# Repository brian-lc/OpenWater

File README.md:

# OpenWater
This is an open source hardware project. It is published under the CERN OpenHardware License. https://www.ohwr.org/documents/294

#Note!
This is very much a work in progress. All designs are subject to change.

## Goal
To create and share an open source water monitoring system that was capable of measuring water temperature, pH, and ORP. 

This repo contains all the hardware, software, 3D models, and instructions on how to create your own version. 

## Bill of Materials (all versions)
https://docs.google.com/spreadsheets/d/1hH_PX7qE9Eqqa5zU-xhwlhM-gbqpwk3e61Kn0q8U03g/edit?usp=sharing

# History

## V3 - Pelican case - WIP
This version rethinks the whole approach and tries to again use a simple enclosure to house the electronics and keep things water-tight. Forget submerged housings and dealing with buoyancy. This will use some foam and the Pelican case to keep the device on top of the water. It'll be bigger but it will also allow the placement of a solar panel on top. 

## V2 - Inflatable 
This design throws away the idea that the enclosure needs to be rigid. Using a flexible tubing (originally designed for industrial processing) I created an enclosure that could be inflated/deflated to adjust for buoyancy. What I learned was that 1) buoyancy is hard to get right when it's a DIY project. Even the slightest off center mass (like a cable on one side) could cause the whole setup to list. Also, USB cables rust. Also also, making something water tight is hard. The first time I floated this in an over-night test the whole inside filled with water because the air pressure stem didn't have enough back-pressure to keep the water out. Luckily none of the electronics were harmed. 

## V1 - Blender Bottle
My first attempt at a cheap ($11 USD) enclosure using an off-the-shelf blender bottle. With just a few components this design came together well but it proved to be too difficult to service the battery. Also, the cabling situation was a nightmare. The probes each come with about 5 feet of coax. Dealing with it is a real pain. 

### Resources and other projects
https://www.voltaicsystems.com/blog/building-solar-powered-cloud-connected-devices/

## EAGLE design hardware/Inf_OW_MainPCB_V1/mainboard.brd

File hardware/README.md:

## Hardware
Here are the eagle source files for the OpenWater PCB. It's a very straightforward design. There are no parts on the PCB itself except for a few pull up resistors (which are not technically needed if you rely on the ones from the internal temp/humidity board by Sparkfun). Also, it has two mount holes placed for easy fastening to an enclosure. See 3D files for details.

The gerbers included here are for version 2 since I used Eagle for V2. For the first version I used Upverter. You can find that project here: https://upverter.com/breakpointer/075962a4a041eaf9/OpenWater_v1/

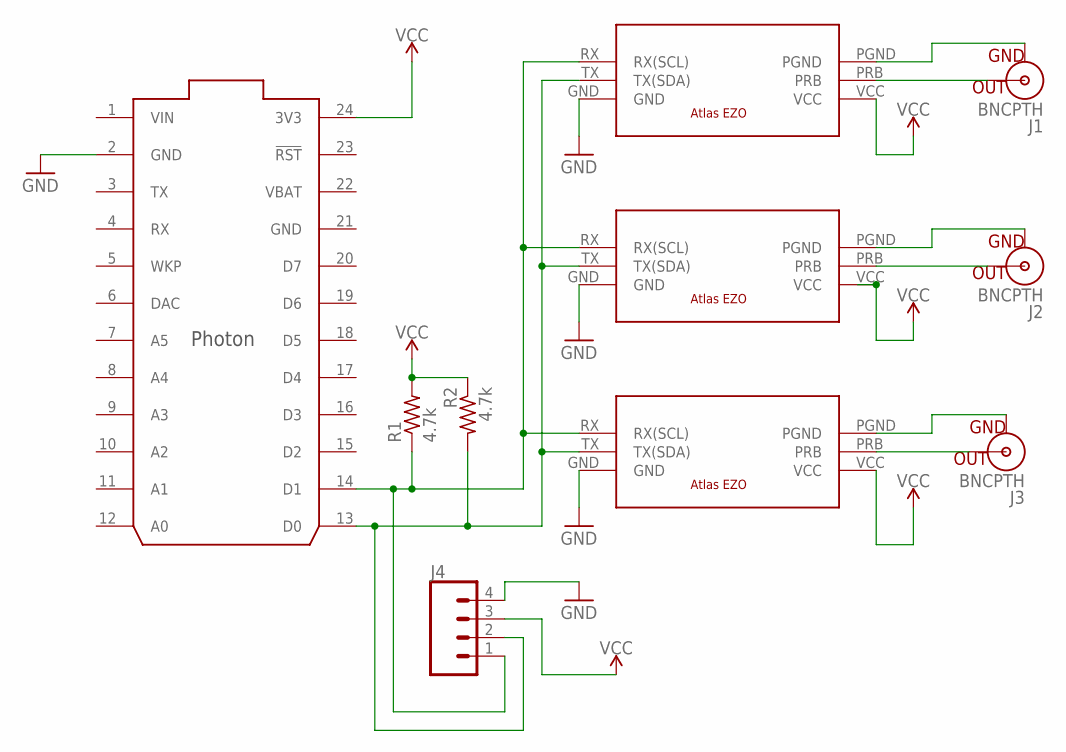
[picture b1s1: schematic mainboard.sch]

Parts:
J1, J2, J3: BNCPTH; BNC
J4: CONN_04; 1X04
R1, R2: 4.7k; 0207/7
U$1: PHOTON_SMD
U$2, U$3, U$4: ATLSCI_EZO; ATLAS_SCI_EZO

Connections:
GND: J4.4, U$1.2 (GND), U$1.21 (GND), U$2.GND, U$3.GND, U$4.GND
unnamed: J4.1, R1.1, U$1.14 (D1), U$2.RX (RX(SCL)), U$3.RX (RX(SCL)), U$4.RX (RX(SCL))
unnamed: J4.2, R2.2, U$1.13 (D0), U$2.TX (TX(SDA)), U$3.TX (TX(SDA)), U$4.TX (TX(SDA))
unnamed: J2.S (OUT), U$3.PRB
unnamed: J2.GND, U$3.PGND
unnamed: J1.S (OUT), U$2.PRB
unnamed: J1.GND, U$2.PGND
unnamed: J3.S (OUT), U$4.PRB
unnamed: J3.GND, U$4.PGND
VBAT: U$1.22 (VBAT)
VCC: J4.3, R1.2, R2.1, U$1.24 (3V3), U$2.VCC, U$3.VCC, U$4.VCC
VIN: U$1.1 (VIN)

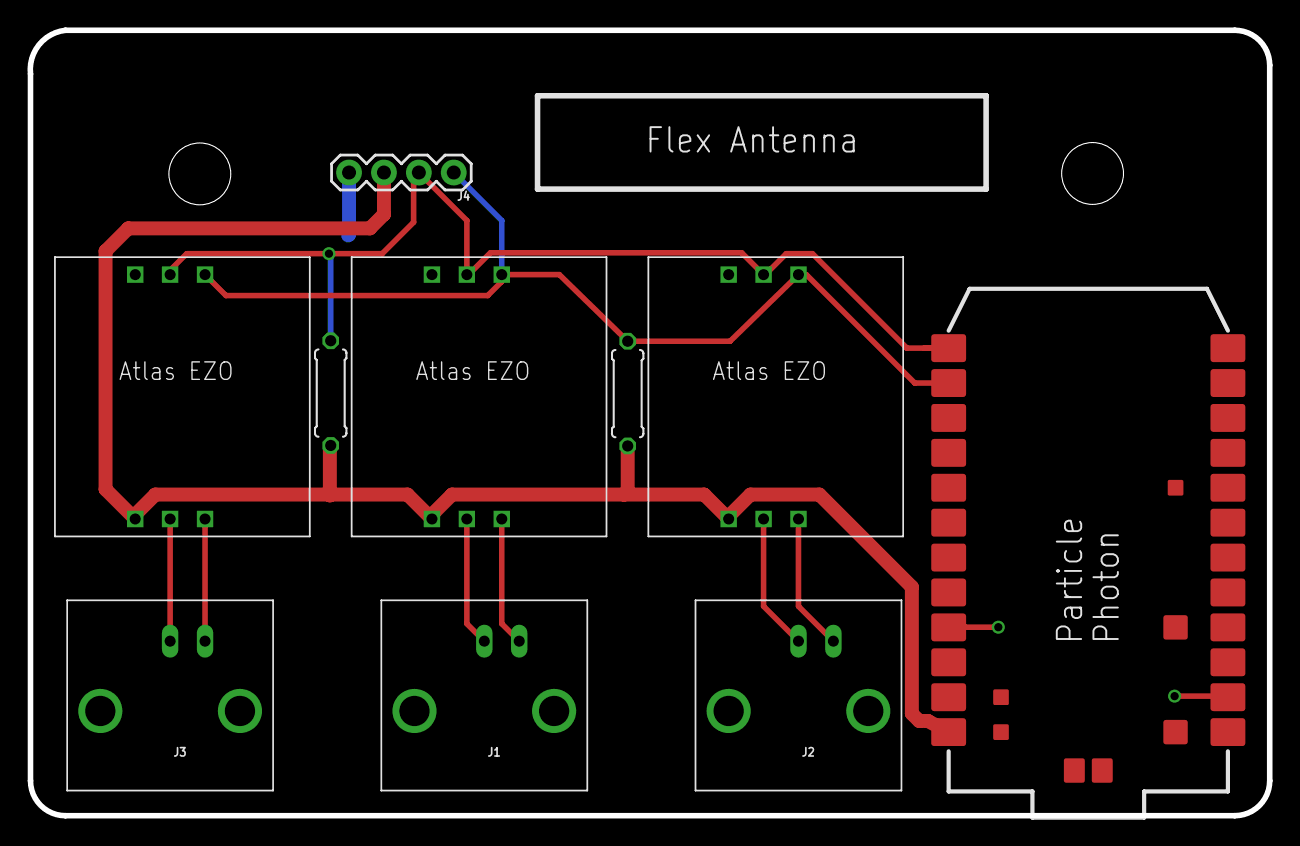
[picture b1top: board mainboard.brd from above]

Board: 2 copper layers, 90.2 x 57.1 mm, 10 parts (0 on the bottom side), 10 nets.

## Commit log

2017-04-12 :octocat: Added .gitattributes
2017-08-23 Added all content, files, images, models created to-date
2017-08-23 Readme update

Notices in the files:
parts and their libraries:
SparkFun-Connectors: Licensing: Creative Commons ShareAlike 4.0 International - https://creativecommons.org/licenses/by-sa/4.0
